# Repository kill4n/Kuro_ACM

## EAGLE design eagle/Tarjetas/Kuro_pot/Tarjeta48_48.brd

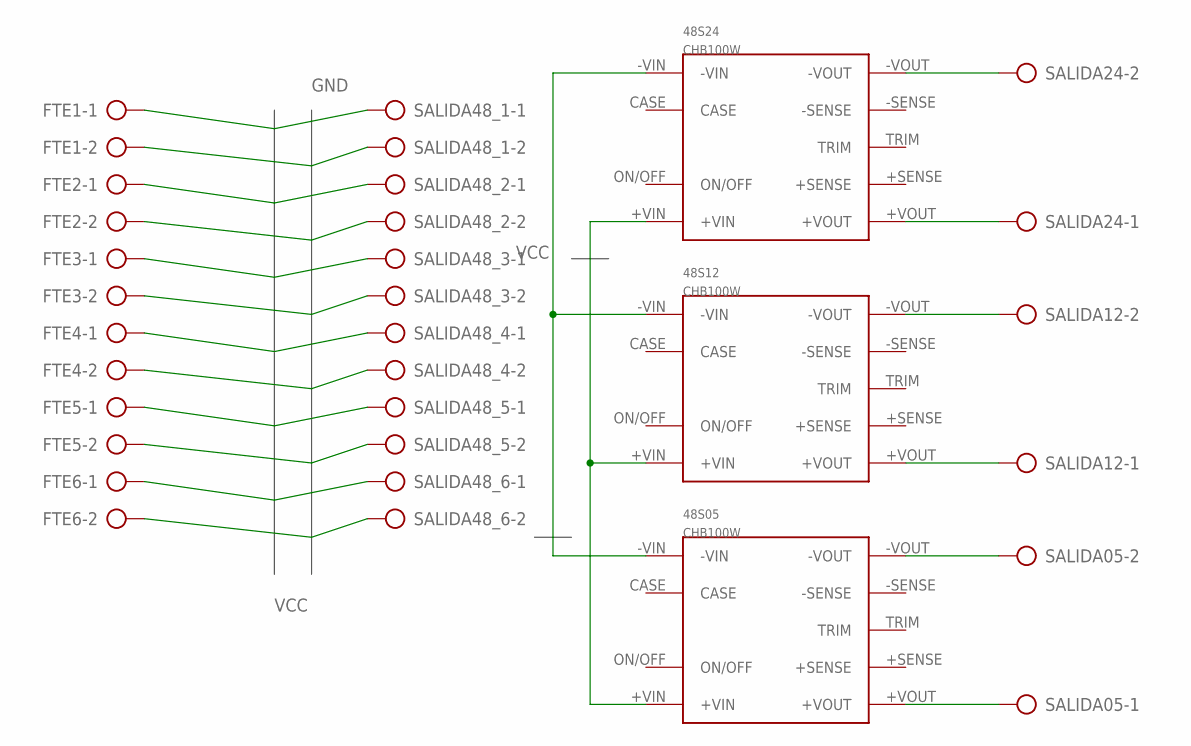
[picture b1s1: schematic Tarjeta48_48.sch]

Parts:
48S05, 48S12, 48S24: CHB100W; CHB
FTE1, FTE2, FTE3, FTE4, FTE5, FTE6: AK500/2-H
SALIDA05, SALIDA12, SALIDA24, SALIDA48_1, SALIDA48_2, SALIDA48_3, SALIDA48_4, SALIDA48_5, SALIDA48_6: AK500/2-H

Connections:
GND: 48S05.-VIN, 48S12.-VIN, 48S24.-VIN, FTE1.2, FTE2.2, FTE3.2, FTE4.2, FTE5.2, FTE6.2, SALIDA48_1.2, SALIDA48_2.2, SALIDA48_3.2, SALIDA48_4.2, SALIDA48_5.2, SALIDA48_6.2
unnamed: 48S05.+VOUT, SALIDA05.1
unnamed: 48S05.-VOUT, SALIDA05.2
unnamed: 48S12.+VOUT, SALIDA12.1
unnamed: 48S12.-VOUT, SALIDA12.2
unnamed: 48S24.+VOUT, SALIDA24.1
unnamed: 48S24.-VOUT, SALIDA24.2
VCC: 48S05.+VIN, 48S12.+VIN, 48S24.+VIN, FTE1.1, FTE2.1, FTE3.1, FTE4.1, FTE5.1, FTE6.1, SALIDA48_1.1, SALIDA48_2.1, SALIDA48_3.1, SALIDA48_4.1, SALIDA48_5.1, SALIDA48_6.1

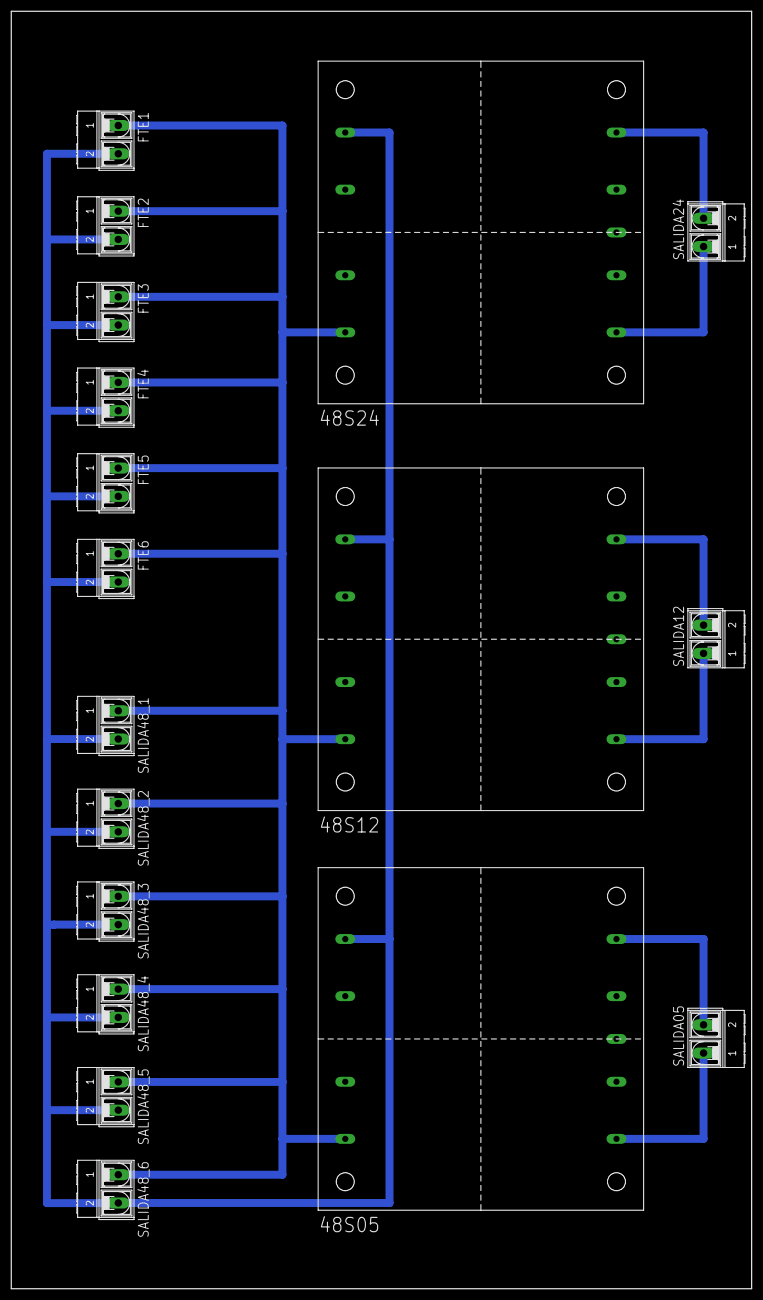
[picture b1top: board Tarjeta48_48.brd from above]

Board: 2 copper layers, 131.8 x 227.3 mm, 18 parts (0 on the bottom side), 8 nets.

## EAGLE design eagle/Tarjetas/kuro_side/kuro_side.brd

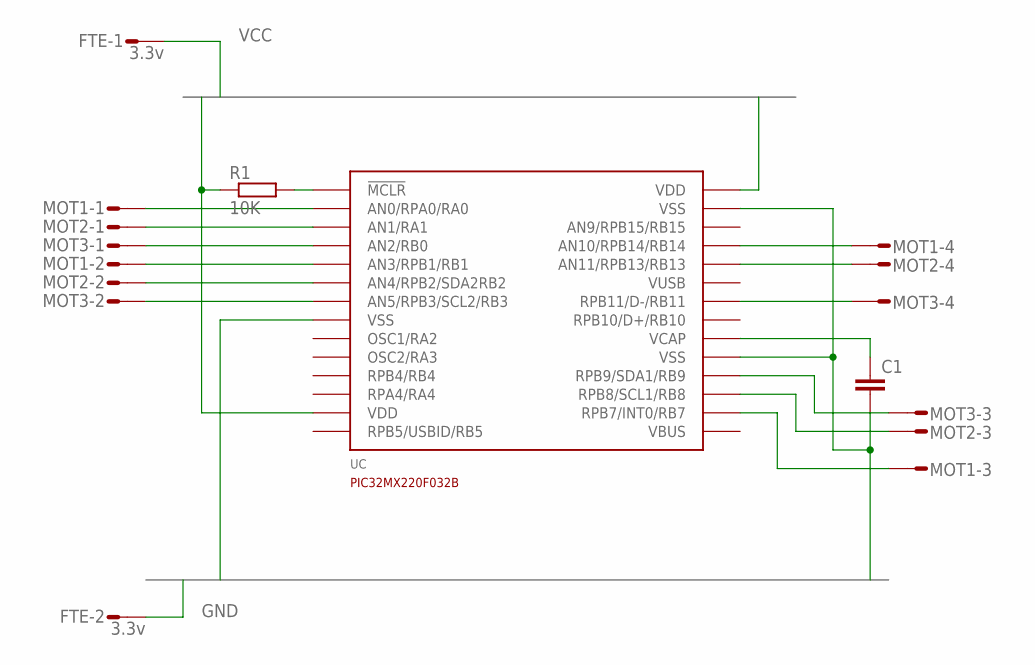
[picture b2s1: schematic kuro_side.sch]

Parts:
C1: C2,5-3; C2.5-3
FTE: 3.3v; S02P
MOT1, MOT2, MOT3: S04P
R1: 10K; 0207/10
UC: PIC32MX220F032B; DIP28

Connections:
GND: C1.2, FTE.2, UC.P$8 (VSS), UC.P$19 (VSS), UC.P$27 (VSS)
unnamed: R1.2, UC.P$1 (!MCLR!)
unnamed: C1.1, UC.P$20 (VCAP)
unnamed: MOT1.1, UC.P$2 (AN0/RPA0/RA0)
unnamed: MOT2.1, UC.P$3 (AN1/RA1)
unnamed: MOT3.1, UC.P$4 (AN2/RB0)
unnamed: MOT1.2, UC.P$5 (AN3/RPB1/RB1)
unnamed: MOT2.2, UC.P$6 (AN4/RPB2/SDA2RB2)
unnamed: MOT3.2, UC.P$7 (AN5/RPB3/SCL2/RB3)
unnamed: MOT3.3, UC.P$18 (RPB9/SDA1/RB9)
unnamed: MOT2.3, UC.P$17 (RPB8/SCL1/RB8)
unnamed: MOT1.3, UC.P$16 (RPB7/INT0/RB7)
unnamed: MOT1.4, UC.P$25 (AN10/RPB14/RB14)
unnamed: MOT2.4, UC.P$24 (AN11/RPB13/RB13)
unnamed: MOT3.4, UC.P$22 (RPB11/D-/RB11)
VCC: FTE.1, R1.1, UC.P$13 (VDD), UC.P$28 (VDD)
VUSB: UC.P$15 (VUSB)

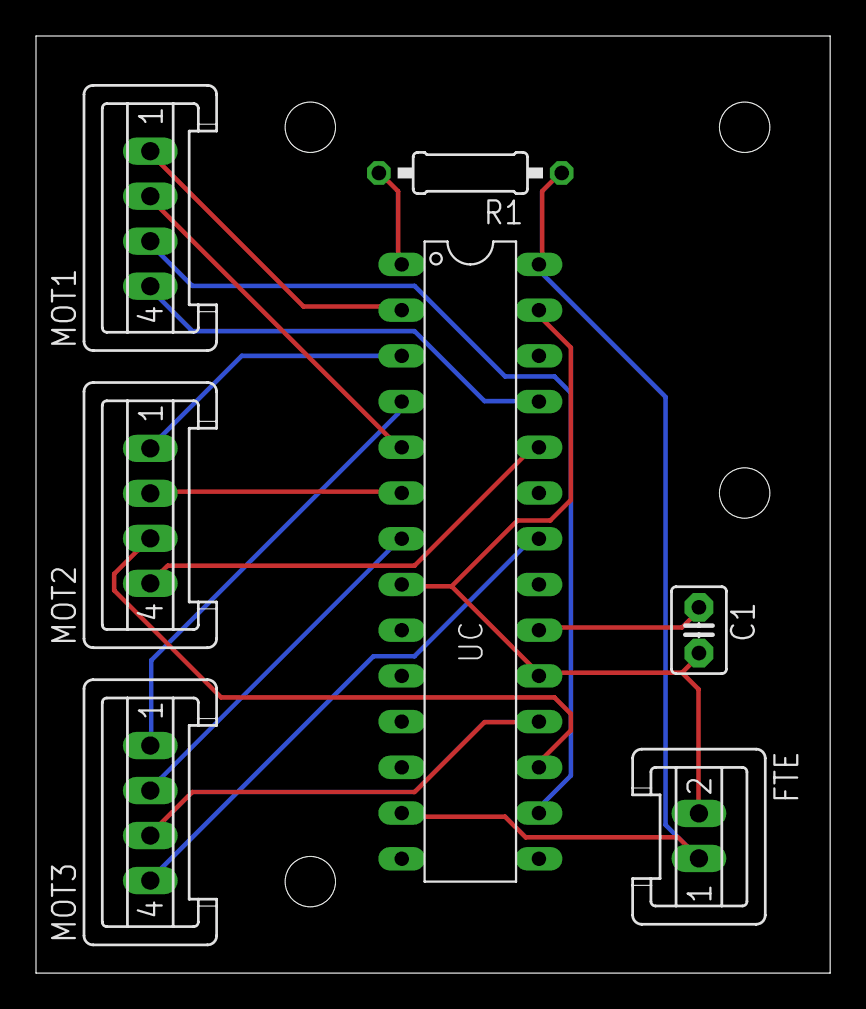
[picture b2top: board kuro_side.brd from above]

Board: 2 copper layers, 44.1 x 52.1 mm, 7 parts (0 on the bottom side), 16 nets.

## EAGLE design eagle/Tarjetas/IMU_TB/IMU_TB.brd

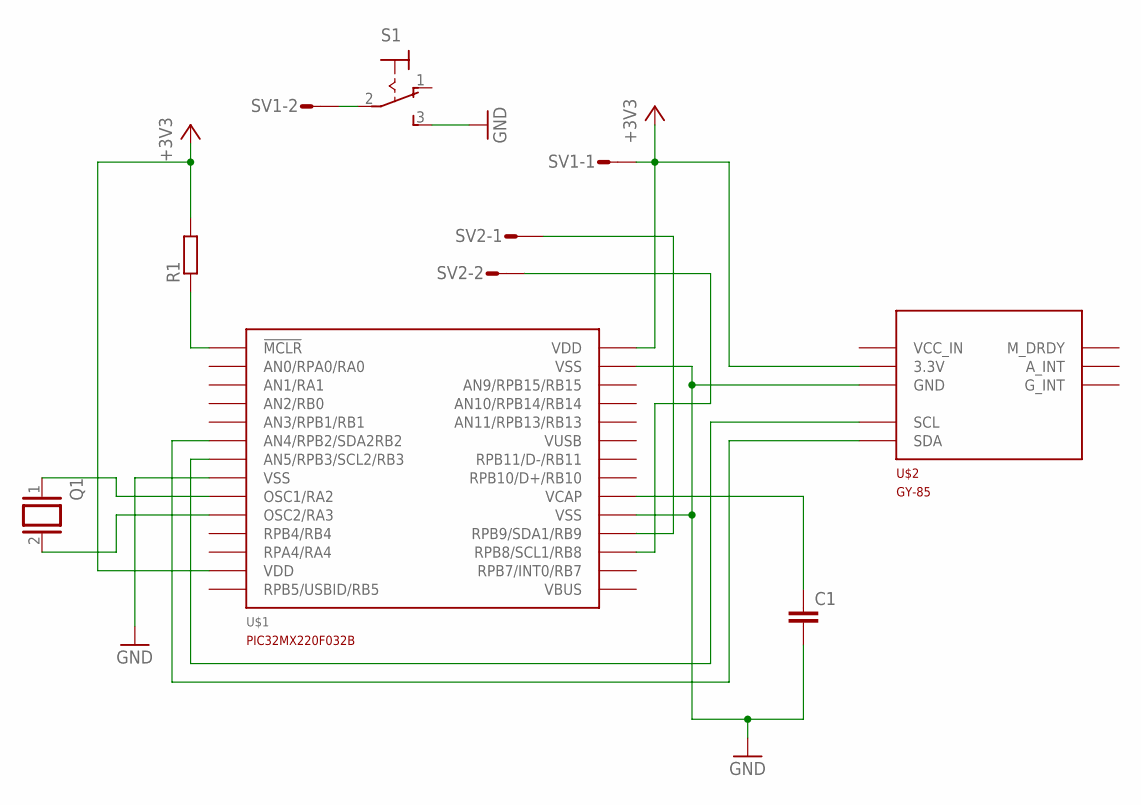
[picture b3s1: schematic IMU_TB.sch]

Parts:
C1: C2,5-3; C2.5-3
Q1: XTAL/S; QS
R1: R-EU_0204/5; 0204/5
S1: 320-916
SV1, SV2: S02P
U$1: PIC32MX220F032B; DIP28
U$2: GY-85

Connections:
+3V3: R1.2, SV1.1, U$1.P$13 (VDD), U$1.P$28 (VDD), U$2.P$2 (3.3V)
GND: C1.2, S1.3 (S), U$1.P$8 (VSS), U$1.P$19 (VSS), U$1.P$27 (VSS), U$2.P$3 (GND)
unnamed: R1.1, U$1.P$1 (!MCLR!)
unnamed: C1.1, U$1.P$20 (VCAP)
unnamed: U$1.P$7 (AN5/RPB3/SCL2/RB3), U$2.P$4 (SCL)
unnamed: U$1.P$6 (AN4/RPB2/SDA2RB2), U$2.P$5 (SDA)
unnamed: Q1.1, U$1.P$9 (OSC1/RA2)
unnamed: Q1.2, U$1.P$10 (OSC2/RA3)
unnamed: SV2.1, U$1.P$18 (RPB9/SDA1/RB9)
unnamed: SV2.2, U$1.P$17 (RPB8/SCL1/RB8)
unnamed: S1.2, SV1.2
VCC_IN: U$2.P$1 (VCC_IN)
VUSB: U$1.P$15 (VUSB)

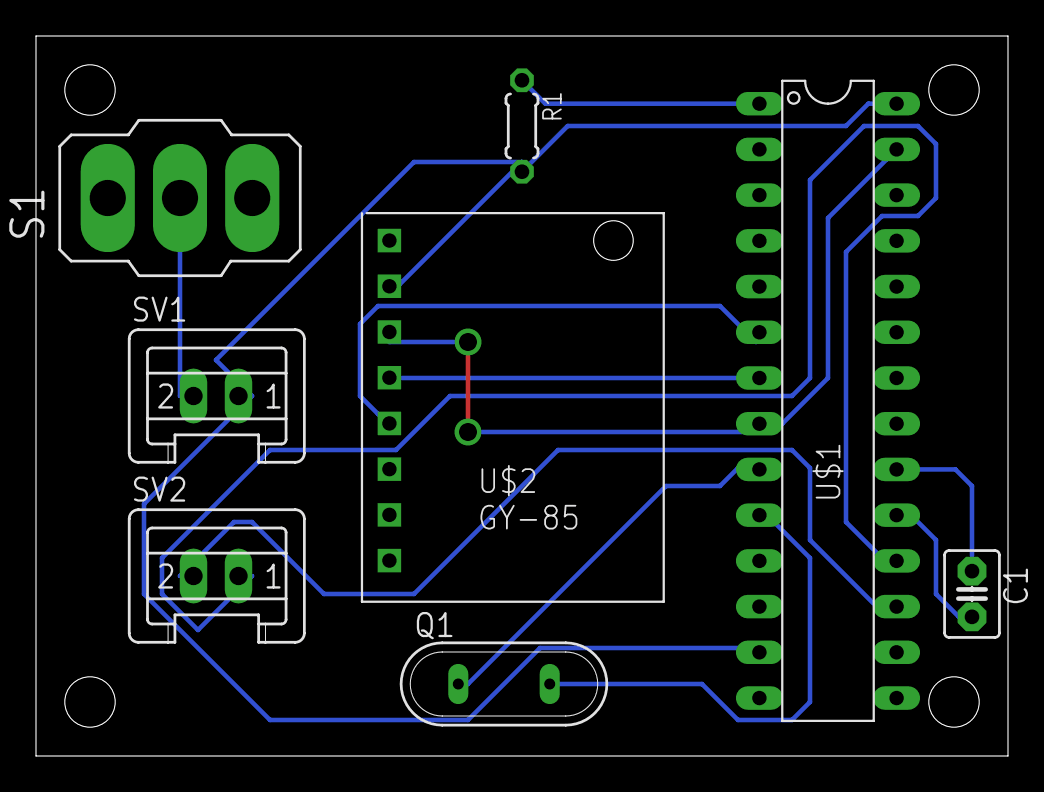
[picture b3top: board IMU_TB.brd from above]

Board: 2 copper layers, 54.0 x 40.0 mm, 8 parts (0 on the bottom side), 11 nets.

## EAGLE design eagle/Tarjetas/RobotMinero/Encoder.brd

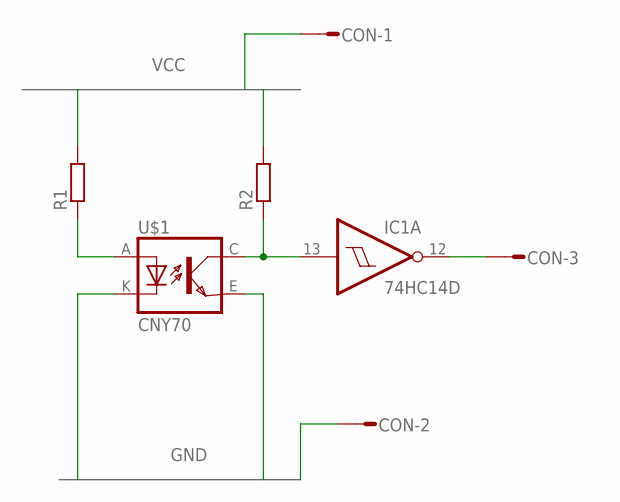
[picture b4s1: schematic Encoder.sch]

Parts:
CON: L03P
IC1: 74HC14D; SO14
R1, R2: R-EU_M1206; M1206
U$1: CNY70; 4

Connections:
GND: CON.2, IC1.7 (GND), U$1.E (EMI), U$1.K (C)
unnamed: R1.1, U$1.A
unnamed: IC1.13 (I), R2.1, U$1.C (COL)
unnamed: CON.3, IC1.12 (O)
VCC: CON.1, IC1.14 (VCC), R1.2, R2.2

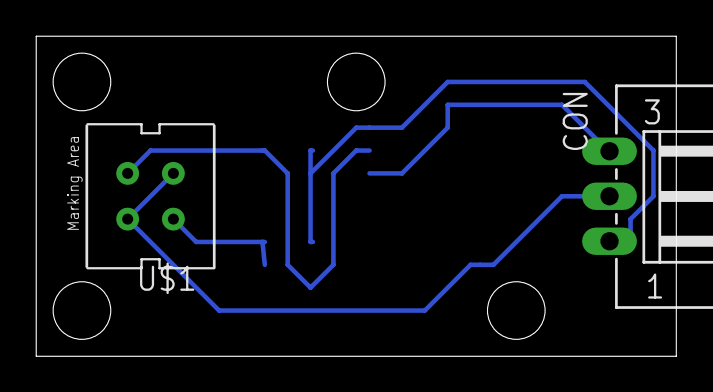
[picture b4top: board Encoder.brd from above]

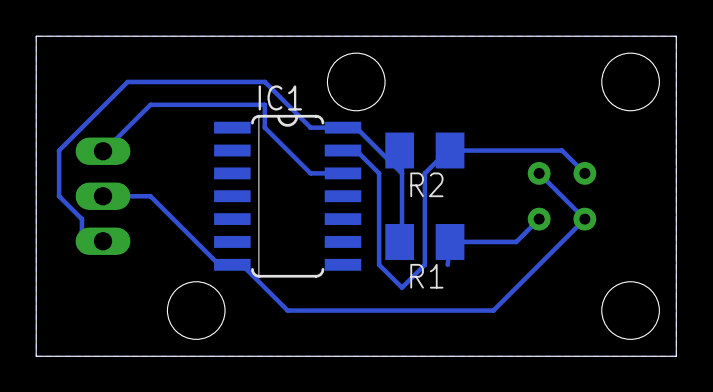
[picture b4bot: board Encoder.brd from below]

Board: 2 copper layers, 35.6 x 17.8 mm, 5 parts (3 on the bottom side), 5 nets.

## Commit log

2015-07-21 Cargar datos desde Dropbox
    Subir todo lo desarrollado en dropbox
2015-07-22 gitIgnore1
2015-07-22 git_ignore_kuro
2015-07-22 Cargar algoritmos para comunicacion con el Laser SICK TIM 350
2015-07-22 igt_ign update
    actulizar gitIgnore
2015-07-31 add OpenCV_joystick Test
2015-08-19 new changes
2015-08-25 aded files
2015-08-25 din1
2015-08-25 din_pro_test1
2015-08-25 Change to Vel
2015-08-25 2000
2015-08-25 cin vel
2015-08-26 new kin
2015-08-28 AX_12 added
2015-08-28 wheel
2015-08-28 spd_var
2015-08-31 Clase AX_12
    Creación clase AX_12 y MotorInterface
    main de ejemplo.
2015-08-31 desde pi2-1
2015-08-31 joint
2015-08-31 update joint
2015-09-01 kuro_core_v2
    version 2 de las carpetas de kuro
2015-09-01 new_structure
2015-09-01 added include
2015-09-01 array
2015-09-01 Ahora en Linux XD
2015-09-01 re_commit
2015-09-01 linux dir y rot
2015-09-01 kuro_lin joy
2015-09-02 motores+Joystic en Linux
2015-09-03 Añadir M54_PRO librerias
2015-09-04 limpiar build
2015-09-04 tratar de agregar la pu"#$"#$"# clase de hilo + camara.
2015-09-14 creación carpetas Uc
2015-09-15 Add uc_migi_1
    migi_hidari
2015-09-15 migi_pc
2015-09-15 3PWM+3SG+3FR_shiro UC
2015-09-15 Harmony
2015-09-15 harm_last
2015-09-16 karmony_led_OK
2015-09-17 Serial_half
2015-09-18 ht_mac
2015-09-30 aassdd
2015-10-06 Camera Thread OK
2015-10-06 Thread Camera OOK
2015-10-09 pic32
2015-10-09 mchp
2015-10-19 shiro imu
2015-10-27 libs eagle
2015-10-27 inicio libs
2015-10-29 dc-dc CHB + board
2015-11-02 c# libros + AG+ chat
2015-11-03 noir sim creacion
2015-11-03 update noir
2015-11-03 noir OK
2015-11-06 ok nov 6
2015-11-08 laser-c++
2015-11-09 migrate laser
2015-11-10 lib sock aux
2015-11-10 sock
2015-11-10 correcion funcion error
2015-11-11 AL creacion matriz
2015-11-11 AL+exceptions+Matriz
    suma
    resta
    producto
    determinante
    excepciones
2015-11-24 mini minero Alive
2015-11-25 ACK+OMN+Dif ok
2015-11-25 cam+ msg
2015-11-25 mensajes
2015-11-28 cambios ver camara
2015-11-29 cam_getresol
2015-12-03 minero + sock
2015-12-03 c++ + camera
2015-12-04 ACM1PT_V2.JPG
2015-12-05 Changes to be committed: modified: kuro_Core/cinematica/acker/include/ackermodel.h modified: kuro_Core/cinematica/acker/src/ackermodel.cpp modified: kuro_Core/cinematica/difer/include/difermodel.h mo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
2015-12-05 flags added
2015-12-06 flags+ send camera RGB
2015-12-06 agregada recepción de imagen
2015-12-08 desde kuro mini
2015-12-09 camara ya envia bien trama
2015-12-09 motor AX-12 BAUD_1Mbps
2015-12-09 flags_ok
2015-12-09 funcionando OK
2015-12-10 pc prog + socket + laser
2015-12-11 dinamixel c#
2015-12-11 dynamixel c# tes OK joint Wheel
2015-12-11 añadir puertos dinamicos
2015-12-11 omni+diff models
2015-12-11 ackerman
2015-12-12 last
2015-12-12 portSelection
2015-12-12 last desde fit
2015-12-12 fit + 3 modos operacuion
2015-12-13 joy+cam
2015-12-13 cam_joy_mot
2015-12-14 last asus
2015-12-14 last_fit
2015-12-14 all to a class miner
2015-12-14 last_fit_14-dic
2015-12-17 last last
2015-12-22 arduino_oki
